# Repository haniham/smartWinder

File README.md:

# smartWinder
A module to smarten up "dumb" (non IOT-able) belt winders

The Project is based on the preliminary work in the FHEM forum which focused on connecting the existing GW60 electronic belt winder by Superrollo: https://forum.fhem.de/index.php/topic,60575.0.html
This repository is meant to keep the relevant information over the existing project and allow forther development.

# Working principle
The existing control unit was kept in place and extended with a secondary ESP8266 WiFi MCU.
Motion of the winder motor is fed in with 2 pins on the ESP.
The position can be determined via an magnetic sensor, either with the integrated hall sensor which is measuring the rotations of the winder or an additional placed hall Sensor which is measuring the rotations of the deflection roller.
The ESP gets control over the movement of the belt winder via two pins which simulate presses on the up and down key.

# Further ideas
- Extending more other comparably working belt winders
- Controlling other Devices which control the position of an object like Garage doors, etc.

# Credits
Great thanks to the FHEM community for all current and furher development and research on the topic https://forum.fhem.de/index.php/topic,60575.0.html

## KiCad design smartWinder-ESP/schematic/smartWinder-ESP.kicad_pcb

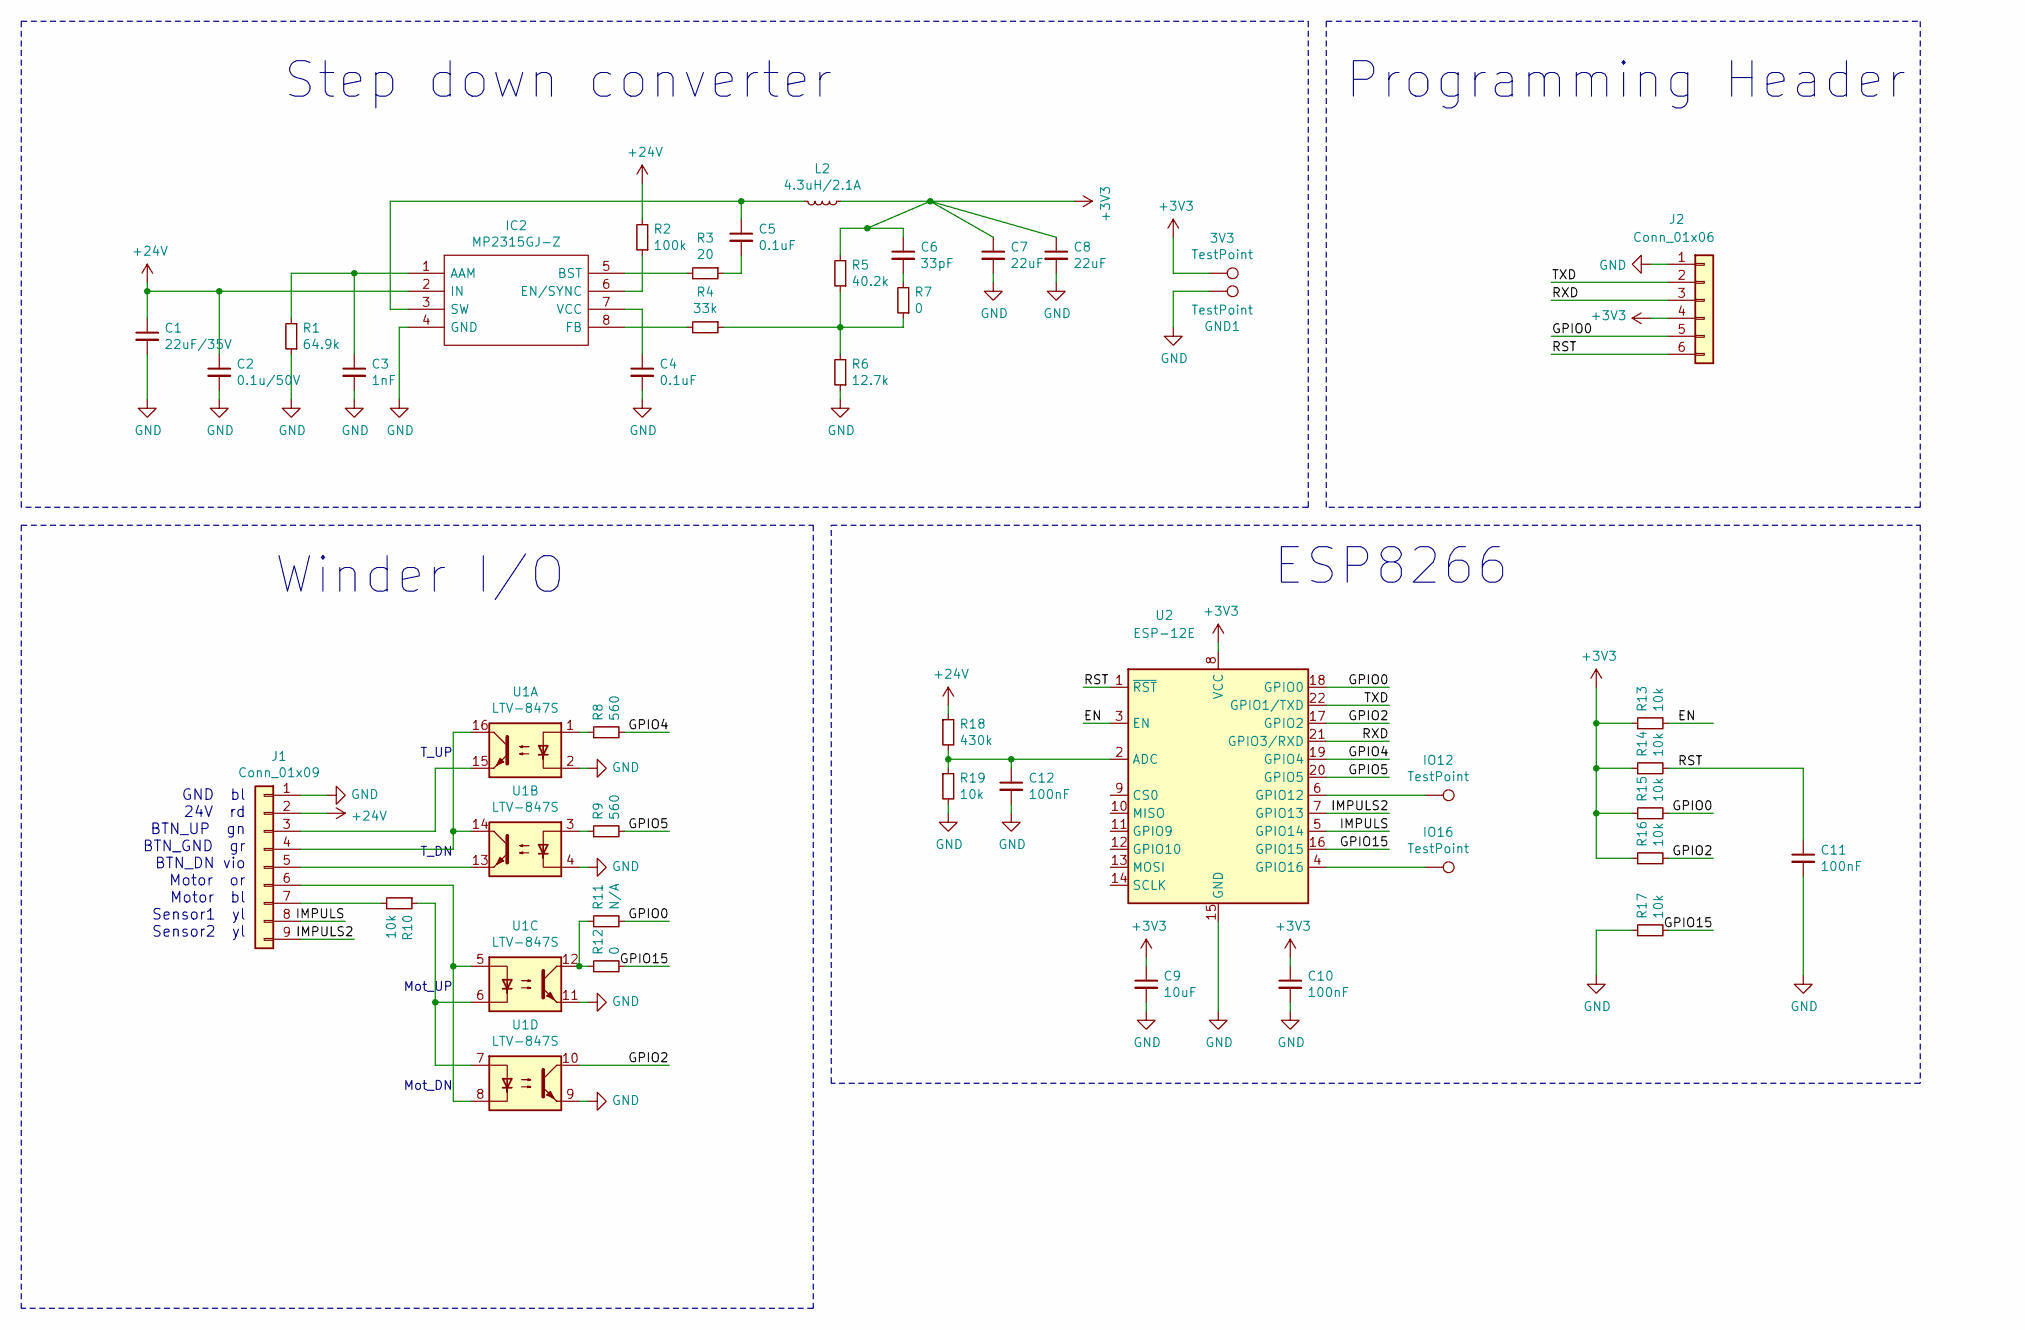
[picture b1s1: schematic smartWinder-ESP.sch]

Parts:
3V3: TestPoint; TestPoint_Pad_D1.0mm
C1: 22uF/35V; C_0805_2012Metric_Pad1.15x1.40mm_HandSolder
C2: 0.1u/50V; C_0805_2012Metric_Pad1.15x1.40mm_HandSolder
C3: 1nF; C_0805_2012Metric_Pad1.15x1.40mm_HandSolder
C4, C5: 0.1uF; C_0805_2012Metric_Pad1.15x1.40mm_HandSolder
C6: 33pF; C_0805_2012Metric_Pad1.15x1.40mm_HandSolder
C7, C8: 22uF; C_0805_2012Metric_Pad1.15x1.40mm_HandSolder
C9: 10uF; C_0805_2012Metric_Pad1.15x1.40mm_HandSolder
C10, C11, C12: 100nF; C_0805_2012Metric_Pad1.15x1.40mm_HandSolder
GND1: TestPoint; TestPoint_Pad_D1.0mm
IC2: MP2315GJ-Z; SOT65P280X100-8N; Manufacturer_Part_Number MP2315GJ-Z
IO12, IO16: TestPoint; TestPoint_Pad_D1.0mm
J1: Conn_01x09; PinHeader_1x09_P2.54mm_Vertical
J2: Conn_01x06; PinHeader_1x06_P2.54mm_Vertical
L2: 4.3uH/2.1A; L_6.3x6.3_H3
R1: 64.9k; R_0805_2012Metric_Pad1.15x1.40mm_HandSolder
R2: 100k; R_0805_2012Metric_Pad1.15x1.40mm_HandSolder
R3: 20; R_0805_2012Metric_Pad1.15x1.40mm_HandSolder
R4: 33k; R_0805_2012Metric_Pad1.15x1.40mm_HandSolder
R5: 40.2k; R_0805_2012Metric_Pad1.15x1.40mm_HandSolder
R6: 12.7k; R_0805_2012Metric_Pad1.15x1.40mm_HandSolder
R7, R12: 0; R_0805_2012Metric_Pad1.15x1.40mm_HandSolder
R8, R9: 560; R_0805_2012Metric_Pad1.15x1.40mm_HandSolder
R10, R13, R14, R15, R16, R17, R19: 10k; R_0805_2012Metric_Pad1.15x1.40mm_HandSolder
R11: N/A; R_0805_2012Metric_Pad1.15x1.40mm_HandSolder
R18: 430k; R_0805_2012Metric_Pad1.15x1.40mm_HandSolder
U1: LTV-847S; SMDIP-16_W9.53mm
U2: ESP-12E

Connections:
+3V3: 3V3.1, C6.1, C7.1, C8.1, C9.1, C10.1, J2.4, L2.1, R5.2, R13.1, R14.1, R15.1, R16.1, U2.8 (VCC)
+24V: C1.1, C2.1, IC2.2 (IN), J1.2, R2.2, R18.1
/EN: R13.2, U2.3 (EN)
/GPIO0: J2.5, R11.2, R15.2, U2.18 (GPIO0)
/GPIO2: R16.2, U1.10, U2.17 (GPIO2)
/GPIO4: R8.2, U2.19 (GPIO4)
/GPIO5: R9.2, U2.20 (GPIO5)
/GPIO15: R12.2, R17.2, U2.16 (GPIO15)
/IMPULS: J1.8, U2.5 (GPIO14)
/IMPULS2: J1.9, U2.7 (GPIO13)
/RST: C11.1, J2.6, R14.2, U2.1 (~RST)
/RXD: J2.3, U2.21 (GPIO3/RXD)
/TXD: J2.2, U2.22 (GPIO1/TXD)
GND: C1.2, C2.2, C3.2, C4.2, C7.2, C8.2, C9.2, C10.2, C11.2, C12.2, GND1.1, IC2.4 (GND), J1.1, J2.1, R1.1, R6.1, R17.1, R19.2, U1.2, U1.4, U1.9, U1.11, U2.15 (GND); also elsewhere on the board
unnamed: C3.1, IC2.1 (AAM), R1.2
unnamed: C4.1, IC2.7 (VCC)
unnamed: C5.1, IC2.3 (SW), L2.2
unnamed: C5.2, R3.1
unnamed: C6.2, R7.2
unnamed: C12.1, R18.2, R19.1, U2.2 (ADC)
unnamed: IC2.5 (BST), R3.2
unnamed: IC2.6 (EN/SYNC), R2.1
unnamed: IC2.8 (FB), R4.2
unnamed: IO12.1, U2.6 (GPIO12)
unnamed: IO16.1, U2.4 (GPIO16)
unnamed: J1.3, U1.15
unnamed: J1.4, U1.14, U1.16
unnamed: J1.5, U1.13
unnamed: J1.6, U1.5, U1.8
unnamed: J1.7, R10.2
unnamed: R4.1, R5.1, R6.2, R7.1
unnamed: R8.1, U1.1
unnamed: R9.1, U1.3
unnamed: R10.1, U1.6, U1.7
unnamed: R11.1, R12.1, U1.12

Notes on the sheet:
GND bl 24V rd BTN_UP gn BTN_GND gr BTN_DN vio Motor or Motor bl Sensor1 yl Sensor2 yl
T_UP
T_DN
Mot_UP
Mot_DN
Step down converter
Programming Header
Winder I/O
ESP8266

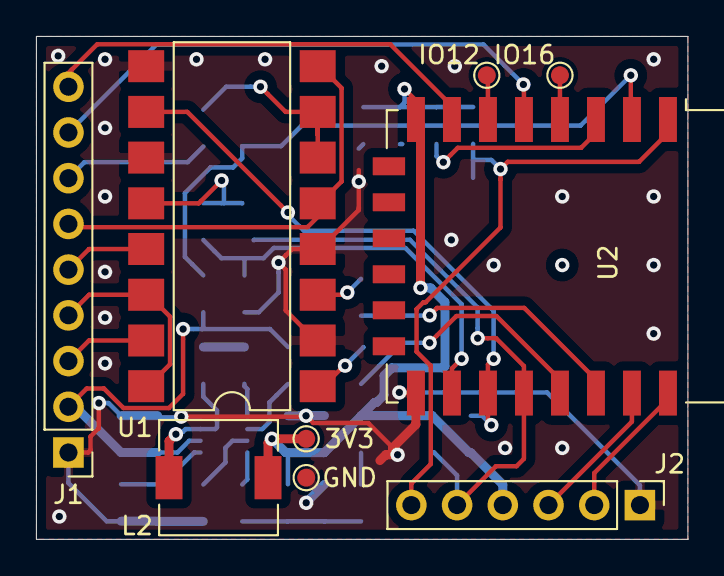
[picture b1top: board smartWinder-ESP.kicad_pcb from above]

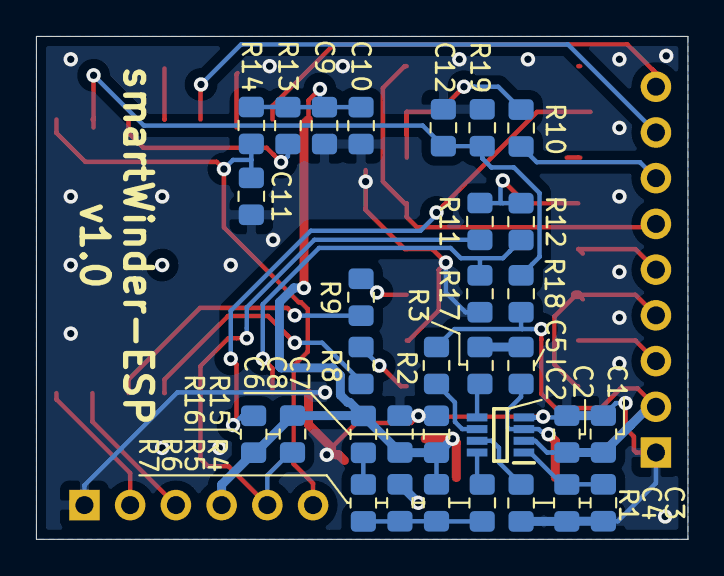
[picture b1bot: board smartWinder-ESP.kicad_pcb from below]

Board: 2 copper layers, 36.2 x 27.9 mm, 41 parts (32 on the bottom side), 35 nets.

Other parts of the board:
GND: TestPoint; TestPoint_Pad_D1.0mm

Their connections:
GND: GND.1; also elsewhere on the board

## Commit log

2019-10-25 Update README.md
    Created first description
2019-10-26 Created Schematic
2019-10-27 Added VIN Sensing to the PCB
2019-10-27 Finalized PCB and sent to Production
    Finalized PCB and sent to Production
    Generated PDF and 3D PCB File
2019-10-27 Merged finalized PCB Design in master branch
